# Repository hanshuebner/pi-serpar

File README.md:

# pi-serpar

This is an extension of the
[pi-parport](https://github.com/worlickwerx/pi-parport) HAT by
WorlickWerx, adding a RS232 serial port to the original design.

WORK IN PROGRESS, DO NOT PRODUCE PCBs FROM THIS YET

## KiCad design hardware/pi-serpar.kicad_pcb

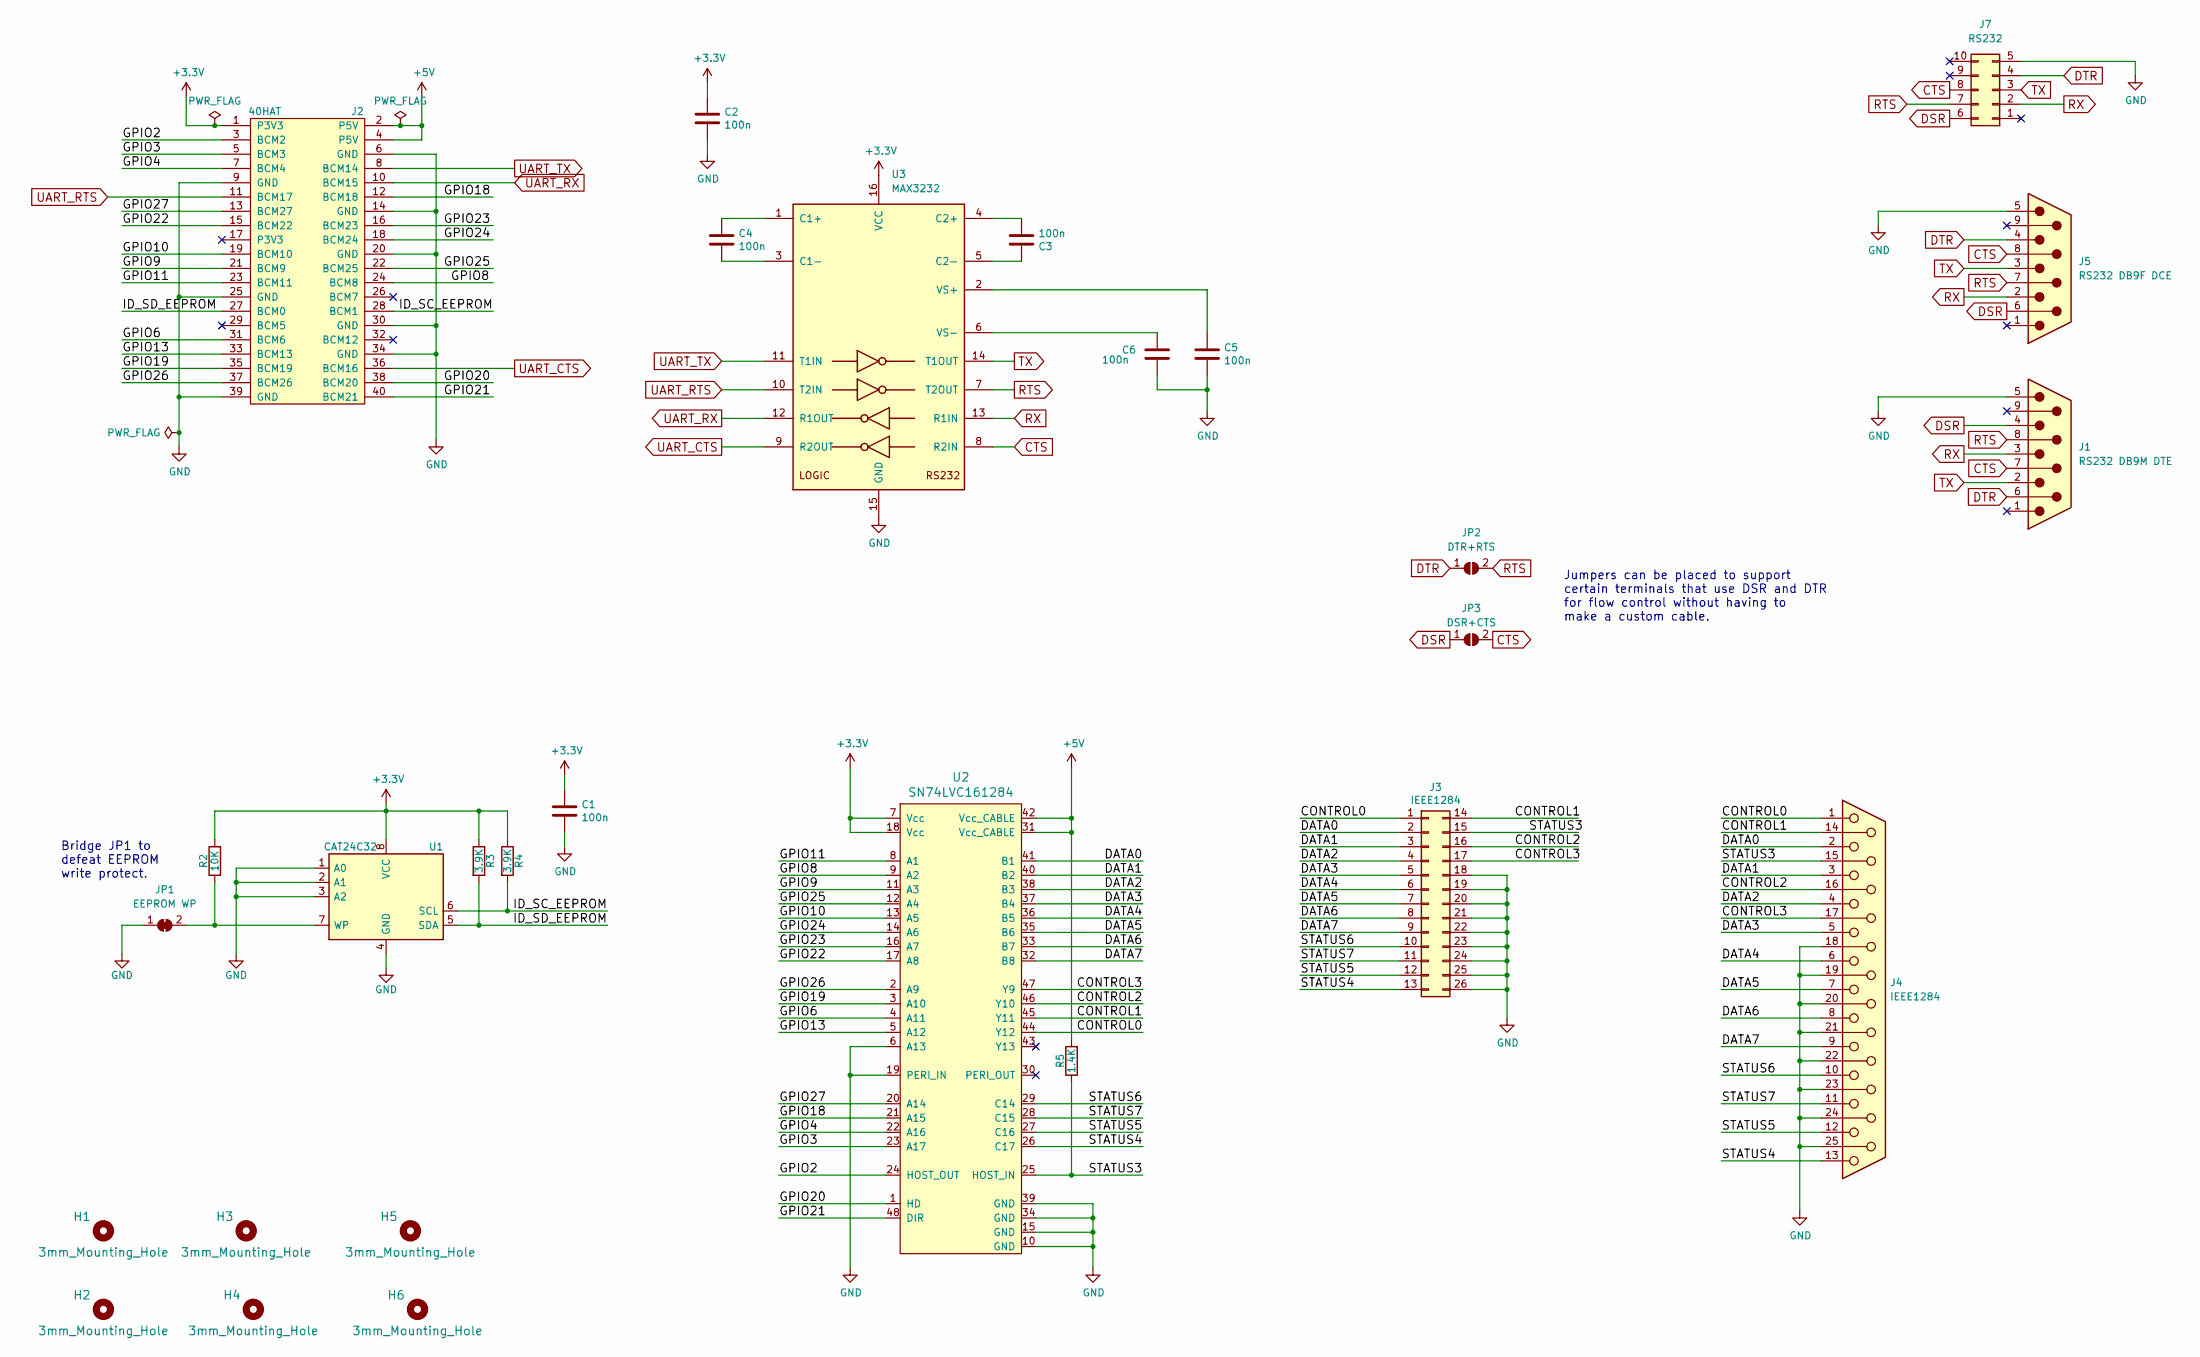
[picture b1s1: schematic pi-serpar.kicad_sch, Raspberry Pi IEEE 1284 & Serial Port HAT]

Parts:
C1, C2, C3, C4, C5, C6: 100n; C_0603_1608Metric_Pad1.08x0.95mm_HandSolder; MPN C0805C104Z5VACTU; Digi-Key_PN 399-1177-1-ND
H1, H2, H3, H4, H5, H6: 3mm_Mounting_Hole; NPTH_3mm_ID
J1: RS232 DB9M DTE; DSUB-9_Male_Horizontal_P2.77x2.84mm_EdgePinOffset7.70mm_Hou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
J2: 40HAT; PinSocket_2x20_P2.54mm_Vertical; MPN PPPC202LFBN-RC; Digi-Key_PN S7123-ND
J3: IEEE1284; PinHeader_2x13_P2.54mm_Vertical; MPN 68021-226HLF; Digi-Key_PN 609-3349-ND
J4: IEEE1284; DSUB-25_Female_Horizontal_P2.77x2.84mm_EdgePinOffset7.70mm_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
J5: RS232 DB9F DCE; DSUB-9_Female_Horizontal_P2.77x2.84mm_EdgePinOffset7.70mm_H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
J7: RS232; PinHeader_2x05_P2.54mm_Vertical
JP1: EEPROM WP; SolderJumper-2_P1.3mm_Bridged_Pad1.0x1.5mm
JP2: DTR+RTS; SolderJumper-2_P1.3mm_Open_RoundedPad1.0x1.5mm
JP3: DSR+CTS; SolderJumper-2_P1.3mm_Open_RoundedPad1.0x1.5mm
R2: 10K; R_0603_1608Metric_Pad0.98x0.95mm_HandSolder; MPN ERJ-6ENF1002V; Digi-Key_PN P10.0KCCT-ND
R3, R4: 3.9K; R_0603_1608Metric_Pad0.98x0.95mm_HandSolder; MPN ERJ-6ENF3901V; Digi-Key_PN P3.90KCCT-ND
R5: 1.4K; R_0603_1608Metric_Pad0.98x0.95mm_HandSolder; MPN ERJ-6ENF1401V; Digi-Key_PN P1.40KCCT-ND
U1: CAT24C32; SOIC-8_3.9x4.9mm_P1.27mm; MPN CAT24C32WI-GT3; Digi-Key_PN CAT24C32WI-GT3CT-ND
U2: SN74LVC161284; TSSOP-48_6.1x12.5mm_P0.5mm; MPN SN74LVC161284DL; Digi-Key_PN 296-8467-5-ND
U3: MAX3232; SO-16_3.9x9.9mm_P1.27mm

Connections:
+3V3: C1.1, C2.1, J2.1 (P3V3), R2.2, R3.1, R4.1, U1.8 (VCC), U2.7 (Vcc), U2.18 (Vcc), U3.16 (VCC)
+5V: J2.2 (P5V), J2.4 (P5V), R5.2, U2.31 (Vcc_CABLE), U2.42 (Vcc_CABLE)
/CONTROL0: J3.1, J4.1, U2.44 (Y12)
/CONTROL1: J3.14, J4.14, U2.45 (Y11)
/CONTROL2: J3.16, J4.16, U2.46 (Y10)
/CONTROL3: J3.17, J4.17, U2.47 (Y9)
/DATA0: J3.2, J4.2, U2.41 (B1)
/DATA1: J3.3, J4.3, U2.40 (B2)
/DATA2: J3.4, J4.4, U2.38 (B3)
/DATA3: J3.5, J4.5, U2.37 (B4)
/DATA4: J3.6, J4.6, U2.36 (B5)
/DATA5: J3.7, J4.7, U2.35 (B6)
/DATA6: J3.8, J4.8, U2.33 (B7)
/DATA7: J3.9, J4.9, U2.32 (B8)
/GPIO2: J2.3 (BCM2), U2.24 (HOST_OUT)
/GPIO3: J2.5 (BCM3), U2.23 (A17)
/GPIO4: J2.7 (BCM4), U2.22 (A16)
/GPIO6: J2.31 (BCM6), U2.4 (A11)
/GPIO8: J2.24 (BCM8), U2.9 (A2)
/GPIO9: J2.21 (BCM9), U2.11 (A3)
/GPIO10: J2.19 (BCM10), U2.13 (A5)
/GPIO11: J2.23 (BCM11), U2.8 (A1)
/GPIO13: J2.33 (BCM13), U2.5 (A12)
/GPIO18: J2.12 (BCM18), U2.21 (A15)
/GPIO19: J2.35 (BCM19), U2.3 (A10)
/GPIO20: J2.38 (BCM20), U2.1 (HD)
/GPIO21: J2.40 (BCM21), U2.48 (DIR)
/GPIO22: J2.15 (BCM22), U2.17 (A8)
/GPIO23: J2.16 (BCM23), U2.16 (A7)
/GPIO24: J2.18 (BCM24), U2.14 (A6)
/GPIO25: J2.22 (BCM25), U2.12 (A4)
/GPIO26: J2.37 (BCM26), U2.2 (A9)
/GPIO27: J2.13 (BCM27), U2.20 (A14)
/ID_SC_EEPROM: J2.28 (BCM1), R4.2, U1.6 (SCL)
/ID_SD_EEPROM: J2.27 (BCM0), R3.2, U1.5 (SDA)
/STATUS3: J3.15, J4.15, R5.1, U2.25 (HOST_IN)
/STATUS4: J3.13, J4.13, U2.26 (C17)
/STATUS5: J3.12, J4.12, U2.27 (C16)
/STATUS6: J3.10, J4.10, U2.29 (C14)
/STATUS7: J3.11, J4.11, U2.28 (C15)
CTS: J1.7, J5.8, J7.8, JP3.2 (B), U3.8 (R2IN)
DSR: J1.4, J5.6, J7.6, JP3.1 (A)
DTR: J1.6, J5.4, J7.4, JP2.1 (A)
GND: C1.2, C2.2, C5.2, C6.2, J1.5, J2.6 (GND), J2.9 (GND), J2.14 (GND), J2.20 (GND), J2.25 (GND), J2.30 (GND), J2.34 (GND), J2.39 (GND), J3.18, J3.19, J3.20, J3.21, J3.22, J3.23, J3.24, J3.25, J3.26, J4.18, J4.19, J4.20, J4.21, J4.22, J4.23, J4.24, J4.25, J5.5, J7.5, JP1.1 (A), U1.1 (A0), U1.2 (A1), U1.3 (A2), U1.4 (GND), U2.6 (A13), U2.10 (GND), U2.15 (GND), U2.19 (PERI_IN), U2.34 (GND), U2.39 (GND), U3.15 (GND)
unnamed: JP1.2 (B), R2.1, U1.7 (WP)
unnamed: C4.1, U3.1 (C1+)
unnamed: C4.2, U3.3 (C1-)
unnamed: C3.2, U3.4 (C2+)
unnamed: C3.1, U3.5 (C2-)
unnamed: C5.1, U3.2 (VS+)
unnamed: C6.1, U3.6 (VS-)
RTS: J1.8, J5.7, J7.7, JP2.2 (B), U3.7 (T2OUT)
RX: J1.3, J5.2, J7.2, U3.13 (R1IN)
TX: J1.2, J5.3, J7.3, U3.14 (T1OUT)
UART_CTS: J2.36 (BCM16), U3.9 (R2OUT)
UART_RTS: J2.11 (BCM17), U3.10 (T2IN)
UART_RX: J2.10 (BCM15), U3.12 (R1OUT)
UART_TX: J2.8 (BCM14), U3.11 (T1IN)

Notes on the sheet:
Bridge JP1 to defeat EEPROM write protect.
Jumpers can be placed to support certain terminals that use DSR and DTR for flow control without having to make a custom cable.

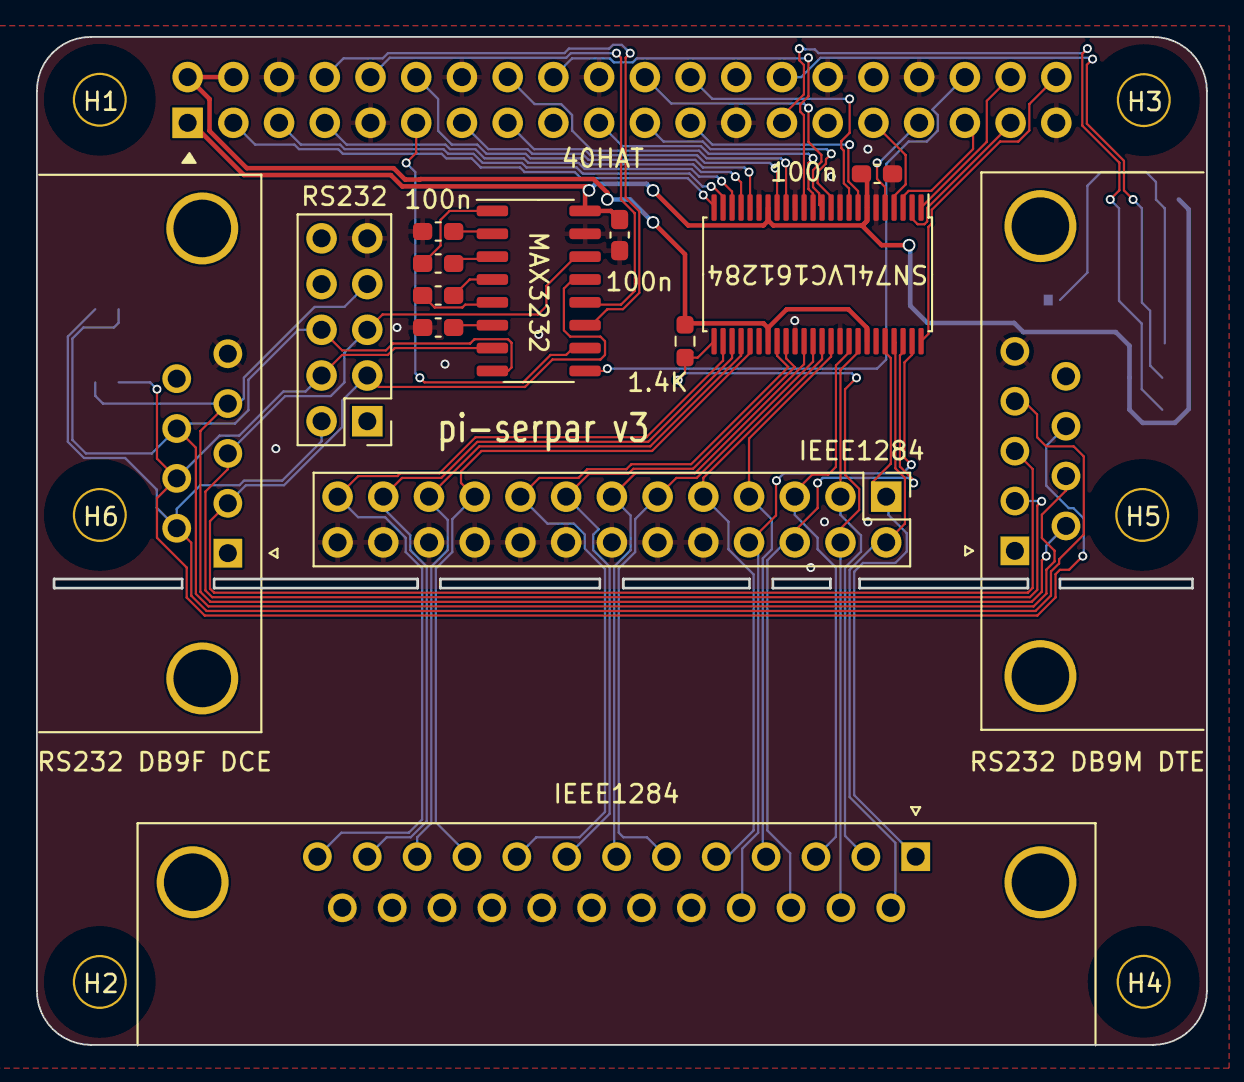
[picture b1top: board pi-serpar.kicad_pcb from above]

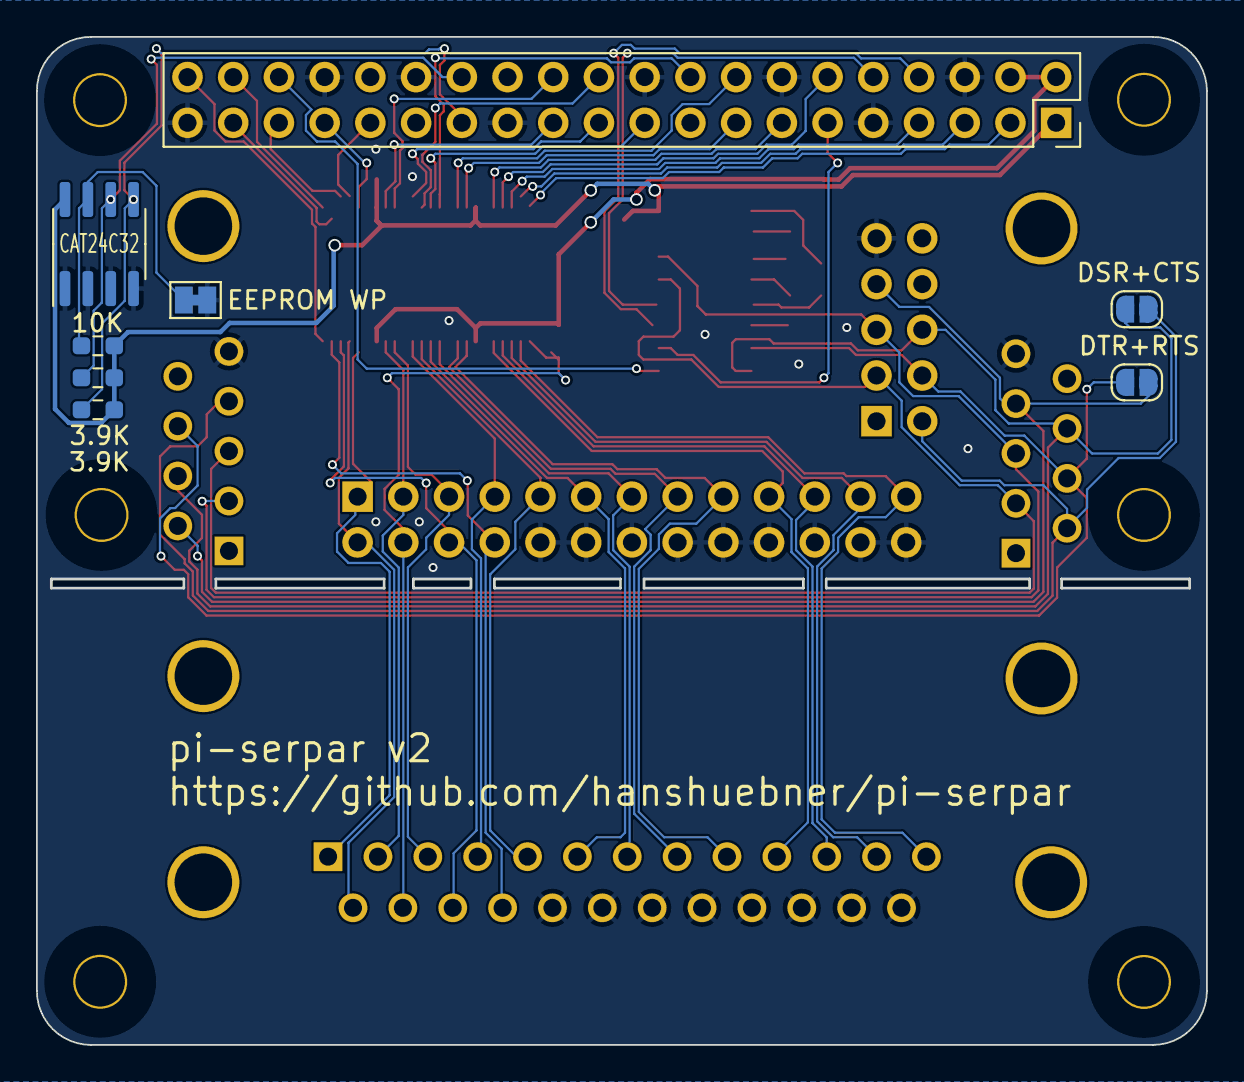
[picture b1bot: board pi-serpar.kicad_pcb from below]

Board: 2 copper layers, 65.0 x 55.9 mm, 28 parts (8 on the bottom side), 58 nets.

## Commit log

2024-03-12 save work
2024-03-12 code golf
2024-03-12 file renames
2024-03-12 v1 ordered at jlcpcb
2024-03-20 IEEE1284 in TSSOP-48 package
2024-04-08 fix idc footprints, add db9h
2024-04-10 v3 with dual db9 footprints
